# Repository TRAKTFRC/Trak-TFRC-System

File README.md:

# Trak-TFRC Product Feature Brief

## Primary goals

To develop and create low power and wireless open source technology that aids in large-scale and long-term wildlife research, conservation, and monitoring the health of ecosystems.
Device list:
1. Lora Base Station
2. TamaCollar
3. SmallCollar
4. MediumCollar
5. Mouse Motel
6. Tamarin Group Monitor  
Names subject to change  

### Device Feature List 

#### LoRa Base Station (AKA LoraTester1) 

A compact, portable device that can transmit and receive Lora messages, as well as store, display, and repeat them.  
- Durable IP66 enclosure with tamper-proof controls and secure mount points  
- LoRa 915Mhz/433Mhz with external SMA antenna mount  
- OLED display  
- SD card for data logging  
- RTC for accurate time keeping  
- GPS module  
- Rechargeable battery for operating in portable mode or when deployed in the field with solar power  
- Multiple modes of operation for receiving & logging LoRa messages, acting as a repeater, or transmitting data.  
- Optional features currently under consideration-  
    - USB connection to allow streaming of LoRa data in realtime to a PC  
    - Operating in a mesh network to extend the range of LoRa Message reception.  

Product usage & lifecycle notes- 
The LT1 units are primarily intended to be either used in handheld mode, or deployed as receivers  near feeding/monitoring sites to receive signals from collars. Ideally they should operate in a mesh to allow us to receive signals over a broader area in the dense amazonian jungle. 
As these are stationary devices mounted either to towers or tall vantage points, maintenance is much easier to perform and we hope these devices can last upwards of 5 years. 
The LT1 is a fairly flexible device, beyond changing it’s operating mode, users may wish to add additional sensors to monitor meteorological data or other.
 
#### TamaCollar

A lightweight tracker collar specifically designed to aid in tracking mature Tamarin species in the Peruvian Amazon.

- IP67 case/resin potting  
- Size- <30*25*6mm  
- Weight- <15g including ball chain collar  
- LoRa 915Mhz/433Mhz  
- RTC for accurate time keeping  
- GPS module  
- Primary non-rechargeable battery  
- User configurable transmission schedule  
- Optional features currently under consideration-  
    - Data logging in case of successful device retrieval

Product usage & lifecycle notes-  
The TC1 units are primarily designed to track wild Emperor Tamarins and Saddleback Tamarins, which are small new world monkeys weighing in at around 500g when grown.  
These lightweight disposable collars are shipped with a magnet taped near the internal reedswitch, and will activate when the vet who’s attaching the devices removes the magnet.   
In most cases, we will be programming the collars and shipping them sealed and ready-to-use, but configurable schedules are preferred. After a period of time, the crimp on the ball chain that holds the collar on will give way and fall off the animal. It is not expected to be recovered in most cases, but in the event that it is recovered, we can take apart the case and reuse the collars with minimal effort.  
Changes to make-  
- We are expecting to add a GPS antenna if required to help improve the GPS lock, both antennas would need to be as low-profile as possible. 
  
#### Tamarin Group Monitor

A deployable station to automate data collection from Tamarins and similar species
- Versatile and reconfigurable for different usecases
- Collects Weight, RFID readings, & images 
- flexible wake triggers
- Transmits data & trigger notifications over LoRa network.

#### SmallCollar

A minute tracker designed to aid in tracking smaller marsupials and rodents under 250g in the Peruvian Amazon.
At present, we are defining the brief for SC1 to allow us to monitor smaller animals than TC1, although no development has taken place yet. The goalposts are flexible so that we can push GPS monitoring to its absolute limits and bring the size and weight down as far as feasible. 
- IP67 case/resin potting  
- Size- TBD  
- Weight- <TBD including ball chain collar  
- LoRa 915Mhz/433Mhz  
- RTC for accurate time keeping  
- GPS module  
- Primary non-rechargeable battery  
- User configurable transmission schedule

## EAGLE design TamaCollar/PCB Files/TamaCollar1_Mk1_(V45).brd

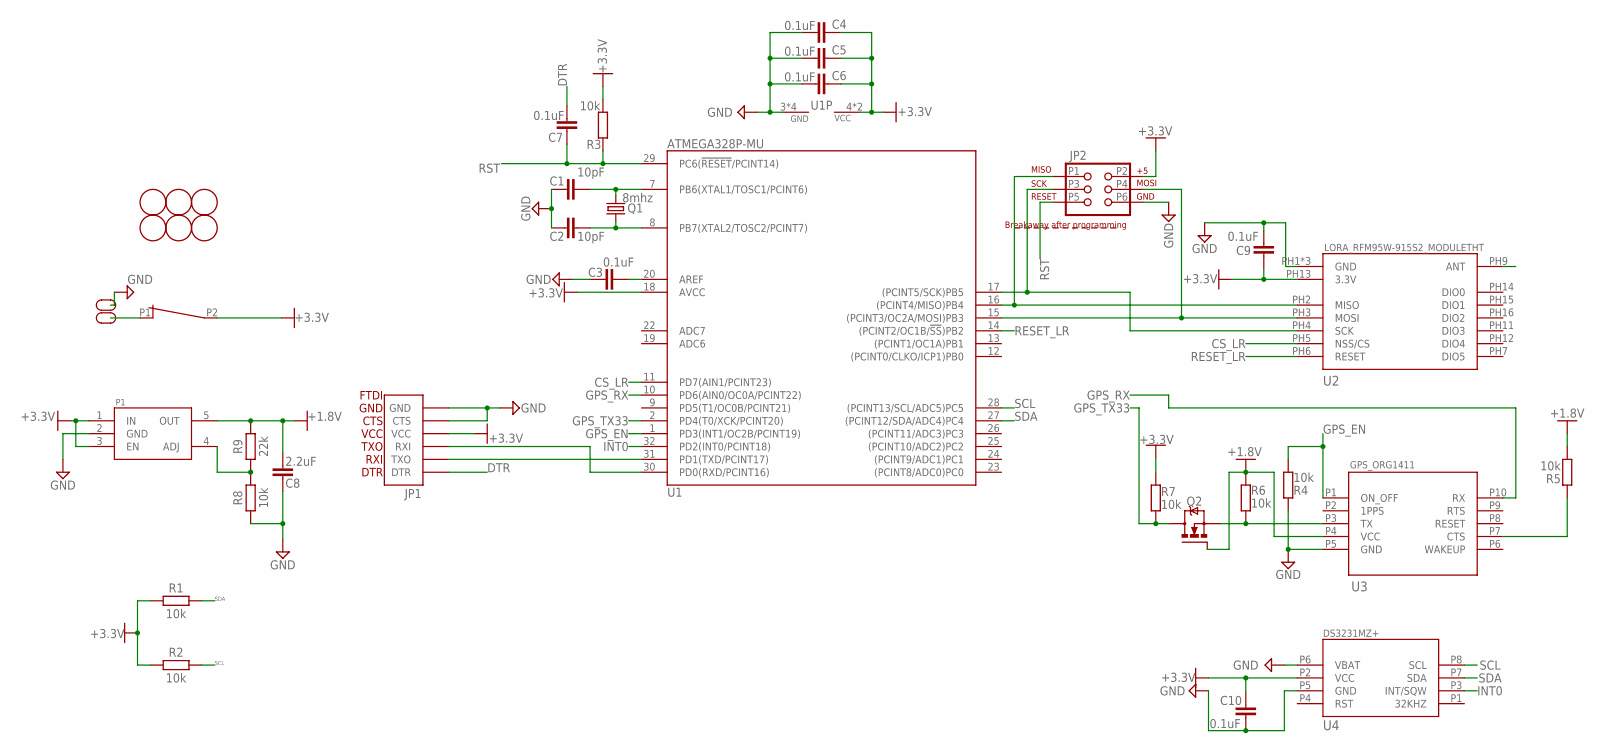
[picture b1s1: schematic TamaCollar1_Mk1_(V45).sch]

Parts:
BATT+: BREAKOUT_PADL; BREAKOUT_PAD*1*1X2MM
BR2: MOUSEBITE3X1.25; MOUSEBITE_3H_6TRACE(1.25MM)
C1, C2: 10pF; CAPC1005X60
C3, C4, C5, C6, C7, C9, C10: 0.1uF; CAPC1005X60
C8: 2.2uF; CAPC1005X60
F1, F2, F3, F4, F5, F6: FIDUCIAL; FIDUCIAL_1MM
GND: BREAKOUT_PADL; BREAKOUT_PAD*1*1X2MM
JP1: FTDI_DEVICESMALL; FTDI_DEVICE_SMD_SMALL
JP2: AVR_SPI_PRG_61X6; 1X6-SMD
P1: LDO_MIC5205YM5; MIC5205
Q1: 8mhz; CRYSTAL_NX3225GD
Q2: NMOSFET; SOT23
R1, R2, R3, R4, R5, R6, R7, R8: 10k; RESC1005X40
R9: 22k; RESC1005X40
SW1: REED_SWITCH; REED_CT05
U1: ATMEGA328P-MU; QFN32_5X5_0.50
U2: LORA_RFM95W-915S2_MODULETHT; LORA_RFM95W-915S2_16STANDOFFMODULE
U3: GPS_ORG1411; ORG1411
U4: DS3231MZ+; DS3231MZ+_SOIC8

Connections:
+1.8V: C8.2, P1.5 (OUT), Q2.1 (G), R5.1, R6.2, R9.2, U3.P4 (VCC)
+3.3V: C4.1, C5.1, C6.1, C9.1, C10.1, JP1.P4 (VCC), JP2.P2 (2), P1.1 (IN), P1.3 (EN), R1.1, R2.1, R3.1, R7.2, SW1.P2 (PAD2), U1.4 (VCC), U1.6 (VCC), U1.18 (AVCC), U2.PH13 (3.3V), U4.P2 (VCC)
+BATT: BATT+.P$1, SW1.P1 (PAD1)
AREF: C3.2, U1.20 (AREF)
CS_LR: U1.11 (PD7(AIN1/PCINT23)), U2.PH5 (NSS/CS)
DTR: C7.2, JP1.P1 (DTR)
GND: C1.1, C2.1, C3.1, C4.2, C5.2, C6.2, C8.1, C9.2, C10.2, GND.P$1, JP1.P5 (CTS), JP1.P6 (GND), JP2.P6 (6), P1.2 (GND), R4.2, R8.1, U1.3 (GND), U1.5 (GND), U1.21 (GND), U1.EXP (GND), U2.PH1 (GND), U2.PH8 (GND), U2.PH10 (GND), U3.P5 (GND), U4.P5 (GND), U4.P6 (VBAT)
GPS_CTS: R5.2, U3.P7 (CTS)
GPS_EN: R4.1, U1.1 (PD3(INT1/OC2B/PCINT19)), U3.P1 (ON_OFF)
GPS_RX: U1.10 (PD6(AIN0/OC0A/PCINT22)), U3.P10 (RX)
GPS_TX18: Q2.2 (S), R6.1, U3.P3 (TX)
GPS_TX33: Q2.3 (D), R7.1, U1.2 (PD4(T0/XCK/PCINT20))
INT0: U1.32 (PD2(INT0/PCINT18)), U4.P3 (INT/SQW)
LR_ANT: U2.PH9 (ANT)
MISO: JP2.P1 (1), U1.16 ((PCINT4/MISO)PB4), U2.PH2 (MISO)
MOSI: JP2.P4 (4), U1.15 ((PCINT3/OC2A/MOSI)PB3), U2.PH3 (MOSI)
P1ADJ: P1.4 (ADJ), R8.2, R9.1
Q1: C1.2, Q1.P2 (2), U1.7 (PB6(XTAL1/TOSC1/PCINT6))
Q2: C2.2, Q1.P1 (1), U1.8 (PB7(XTAL2/TOSC2/PCINT7))
RESET_LR: U1.14 ((PCINT2/OC1B/!SS!)PB2), U2.PH6 (RESET)
RST: C7.1, JP2.P5 (5), R3.2, U1.29 (PC6(!RESET!/PCINT14))
RXD: JP1.P3 (RXI), U1.30 (PD0(RXD/PCINT16))
SCK: JP2.P3 (3), U1.17 ((PCINT5/SCK)PB5), U2.PH4 (SCK)
SCL: R2.2, U1.28 ((PCINT13/SCL/ADC5)PC5), U4.P8 (SCL)
SDA: R1.2, U1.27 ((PCINT12/SDA/ADC4)PC4), U4.P7 (SDA)
TXD: JP1.P2 (TXO), U1.31 (PD1(TXD/PCINT17))

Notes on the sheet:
FTDI GND CTS VCC TXO RXI DTR

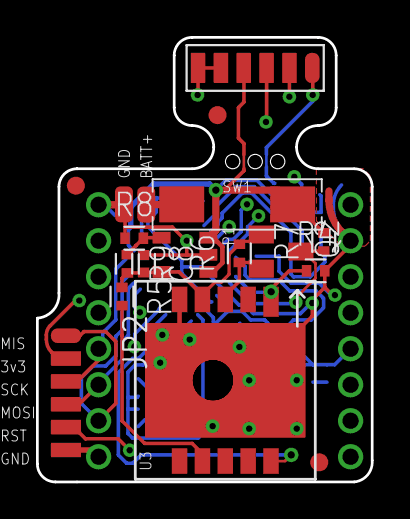
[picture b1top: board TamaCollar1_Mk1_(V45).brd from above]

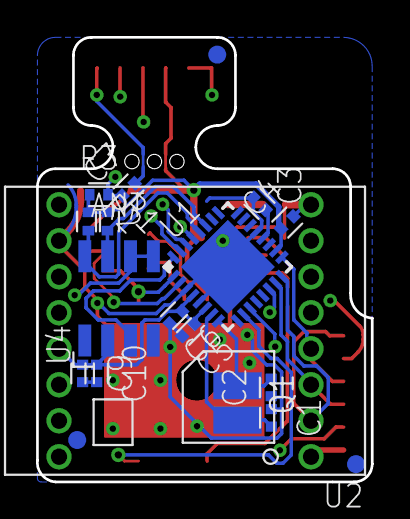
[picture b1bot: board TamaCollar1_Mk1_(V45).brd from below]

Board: 4 copper layers, 18.6 x 24.7 mm, 38 parts (19 on the bottom side), 25 nets.

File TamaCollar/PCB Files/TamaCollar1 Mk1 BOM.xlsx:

Board Qty- | 10
Ordering Quantity | Qty | Value | Device | Package | Parts | Description | LINK
70 | 7 | 0.1uF | C_CHIP-0402(1005-METRIC) | CAPC1005X60 | C3, C4, C5, C6, C7, C9, C10 | Capacitor - Generic | https://www.evelta.com/100-nf-25v-0402-smd-multi-layer-ceram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
80 | 8 | 10k | R_CHIP-0402(1005-METRIC) | RESC1005X40 | R1, R2, R3, R4, R5, R6, R7, R8 | Resistor Fixed - Generic | https://www.evelta.com/10k-1-0402-smd-thick-film-chip-resist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
20 | 2 | 10pF | C_CHIP-0402(1005-METRIC) | CAPC1005X60 | C1, C2 | Capacitor - Generic | https://www.evelta.com/10-pf-50v-0402-smd-multilayer-ceramic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
10 | 1 | 2.2uF | C_CHIP-0402(1005-METRIC) | CAPC1005X60 | C8 | Capacitor - Generic | Out of stock, will need to order from SP road.
10 | 1 | 22k | R_CHIP-0402(1005-METRIC) | RESC1005X40 | R9 | Resistor Fixed - Generic | https://www.evelta.com/22k-1-0402-smd-thick-film-chip-resist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
10 | 1 | 8mhz | CRYSTAL | CRYSTAL_NX3225GD | Q1 | CRYSTAL | https://www.evelta.com/nx3225gd-8mhz-std-cra-3-8mhz-50ppm-cr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
10 | 1 | ATMEGA328P-MU | ATMEGA328P-MU | QFN32_5X5_0.50 | U1 | 8-bit AVR Microcontroller | https://www.rhydolabz.com/components-microcontrollers-c-172_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
10 | 1 | DS3231MZ+ | DS3231MZ+ | DS3231MZ+_SOIC8 | U4 |  | https://www.evelta.com/ds3231mz-maxim-integrated-alarm-rtc-i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
10 | 1 | GPS_ORG1411 | GPS_ORG1411 | ORG1411 | U3
10 | 1 | LDO_MIC5205YM5 | LDO_MIC5205YM5 | MIC5205 | P1 |  | https://www.evelta.com/mic5205ym5-adjustable-ldo-voltage-reg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
10 | 1 | LORA_RFM95W-915S2_MODULETHT | LORA_RFM95W-915S2_MODULETHT | LORA_RFM95W-915S2_16STANDOFFMODULE | U2 |  | https://www.digikey.in/product-detail/en/rf-solutions/RFM95W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
10 | 1 | NMOSFET | NMOSFETSOT23 | SOT23 | Q2 | N-Channel MOSFET - Generic | https://www.evelta.com/bss138lt1g-50v-220ma-n-channel-transi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
10 | 1 | REED_SWITCH | REED_SWITCH | REED_CT05 | SW1

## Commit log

2021-08-23 Added base files
2021-08-23 Formatting
2021-12-16 adds the firmware for TamaCollar developed on GCC
2021-12-17 adds logic for medium collar in firmware and lora based time update in progress
2021-12-17 adds process to update time using lora packet
2021-12-17 adds seperate makefiles created for tama collar and medium collar
2021-12-17 adds readme to firmware directory containing build instructions
2021-12-27 adds changes to make release and GPS work
2021-12-28 adds cahnges to make GPS work
2021-12-28 adds the ardino as isp code to be used
2021-12-29 Updating documentation for LBS, TC
    Updated documentation, production files, and reorganized files in general.
    From henceforth the git repo will be used for maintaining fabrication details, and the g.drive for internal documents.
2021-12-31 changes to make GPS and LoRa work on Medium collar
2021-12-31 Updated TC and LBS hardware files
    Added TC hardware assembly notes
    Updated hardware TC1 to TC1.1A
    Updated hardware LBS1 to LBS1.2 (pending minor alignment revision)
2022-01-01 Added MC1 & MC1.1
    I've added MC1 and MC1.1 as two similar but distinct collars, along with their own documentation.
    MC1.1 is still WIP at the moment.
2022-01-03 Improved changelog and removed erroneous component
    LBS1.2 C6 had a old entry, removed now.
2022-01-06 minor firmware changes
2022-01-07 recompliles the tama collar
2022-01-07 changes for testing tama collar
2022-01-08 adds feature to check serial string to see if gps is on or off after pulse
2022-01-08 bug fixes according in wake and sleep detection logic
2022-01-10 changes to make voltage reading work
2022-01-10 LBS
    Fixed error in LBS BOM
    BOM and PBS for TGM are WIP.
2022-01-10 Updated MC and LBS
    LBS1.2 to 1.3
    MC1.1 to 1.2
    Added 470R resistors to mosfets to limit inrush
2022-01-11 Processed TGM files
    TGM files are ready for production now.
2022-01-13 changes the schedule and time will be set to wake time if time dosen't get set by lora and GPS. Also time update to latest GPS time everytime wwoke up and gps acquired
2022-01-21 bug fixes in scheduling caluculation
2022-01-21 changes collar if
2022-01-27 Added TGM Production files
    Added fab files for TGM's case, and updating MC1.1's PBS. TGM PBS is WIP.
2022-01-28 MC1.1 & TGM tweaks
    Tweaked MC1.1 to improve prints
    TGM PBS updated,
2022-03-26 changing over the laptop
2022-03-28 adds code for EEPROM and packets for setting schedule and dev id. They get stored in EEPROM
2022-03-29 Updated MC1.1 PCB Rev1.2
    - Added Inrush resistors R8 & R9
2022-04-05 adds EEPROM and packet based config for RTC device ID and schedule
2022-04-08 updates the packet defination, load schedule from eeprom at start of program and enable the change in bandwidth of lora transmission and recieving setting
2022-04-09 make the packet buffer bigger to accomodate schedule packet or such bigger packet
2022-04-10 zero the buffer at detect soh
2022-04-14 remove timestamp from packet and fix the schedule loading from eeprom issue
2022-04-14 remove timestamp from location packet also
2022-04-19 needed to commit to able to revert
2022-04-19 Revert "remove timestamp from location packet also"
    This reverts commit 7711d55858ba2fcec815280fd4b7b6c759ebdfec.
2022-04-19 Revert "remove timestamp from packet and fix the schedule loading from eeprom issue"
    This reverts commit ee7482e2b9fac6564cebf0d8540ea3f18cf93960.
2022-04-19 Revert "zero the buffer at detect soh"
    This reverts commit 04a2890ef193798a3a9b290a6757ee8f7bb4de92.
2022-04-19 Revert "needed to commit to able to revert"
    This reverts commit 3da658883bd722abb96322932c6b883644b48a7a.
2022-04-23 adds code for storing data point in external eeprom for medium collar
2022-04-24 immproves RAM usage and changes in firmware to test the EEPROM, these changes will be reverted so this commit is not usable for testing of normal fuctionality of tamacollar and medium collar
2022-04-25 Tama and medium collar firmware with RAM optimization and working without external eeprom functionality
2022-04-25 with default schedule if no schedule set. Ignore the printing it's bit weird right now due to RAM optimization thing
2022-04-25 some fixes in printing
2022-04-25 automate the changing of device code during compile
2022-04-26 adds comma in no loc packet to align the part of packet in excel
2022-04-27 adds functions of external eeprom and dump command during start of firmare
2022-05-05 changes in wakeup packet
2022-08-17 Expanded collar enclosures
    Added updated enclosures used during 2022 trials.
2022-10-04 splits the tama collar and medium collar formware and adds packet queing mechanism to the medium collar
2022-11-03 fixes bugs in the packet generator
2022-11-18 updates ack packet detection, adds date to the packet
2022-11-22 makes the year into 4 digit in date of packet
2023-01-15 recheck buffer lengths and fixes in the packet generation
2023-01-15 fixes some debugging msg which were causing confusion
2023-01-15 adds special hex to delete packets
2023-01-16 changes delay for waiting for the ack from 3 secs to 10 secs
2023-02-17 adds back start storing function in packet processing
2023-02-20 Shifted firmware folders
    I've shifted the tamacollar_firmware & mediumcollar_firmware to their *device*/software folders to keep things organized.
2023-02-20 Cleaning up
    Cleaned up some leftover files.
